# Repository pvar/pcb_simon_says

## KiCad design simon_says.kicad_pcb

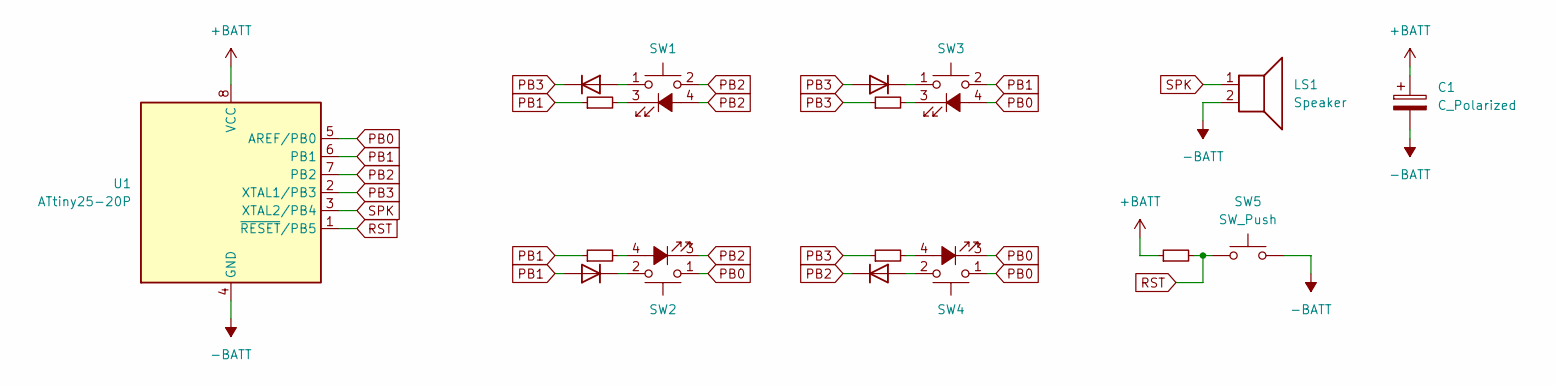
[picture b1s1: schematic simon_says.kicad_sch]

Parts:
C1: C_Polarized
D1, D2, D3, D4: 1N4004; D_DO-34_SOD68_P7.62mm_Horizontal
LS1: Speaker; PinHeader_1x02_P2.54mm_Vertical
R1, R2, R3, R4, R5: 50R; R_Axial_DIN0207_L6.3mm_D2.5mm_P7.62mm_Horizontal
SW1, SW2, SW3, SW4: SW_Push_LED; FX_tactile_12mm_with_LED
SW5: SW_Push; SW_MEC_5GSH9
U1: ATtiny25-20P; DIP-8_W7.62mm

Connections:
+BATT: C1.1, R5.1, U1.8 (VCC)
-BATT: C1.2, LS1.2, SW5.2, U1.4 (GND)
unnamed: D1.2 (A), SW1.1
unnamed: D2.1 (K), SW3.1
unnamed: D3.1 (K), SW2.2
unnamed: D4.2 (A), SW4.2
unnamed: R2.2, SW1.3 (K)
unnamed: R3.2, SW2.4 (A)
unnamed: R1.2, SW3.3 (K)
unnamed: R4.2, SW4.4 (A)
PB0: SW2.1, SW3.4 (A), SW4.1, SW4.3 (K), U1.5 (AREF/PB0)
PB1: D3.2 (A), R2.1, R3.1, SW3.2, U1.6 (PB1)
PB2: D4.1 (K), SW1.2, SW1.4 (A), SW2.3 (K), U1.7 (PB2)
PB3: D1.1 (K), D2.2 (A), R1.1, R4.1, U1.2 (XTAL1/PB3)
RST: R5.2, SW5.1, U1.1 (~RESET/PB5)
SPK: LS1.1, U1.3 (XTAL2/PB4)

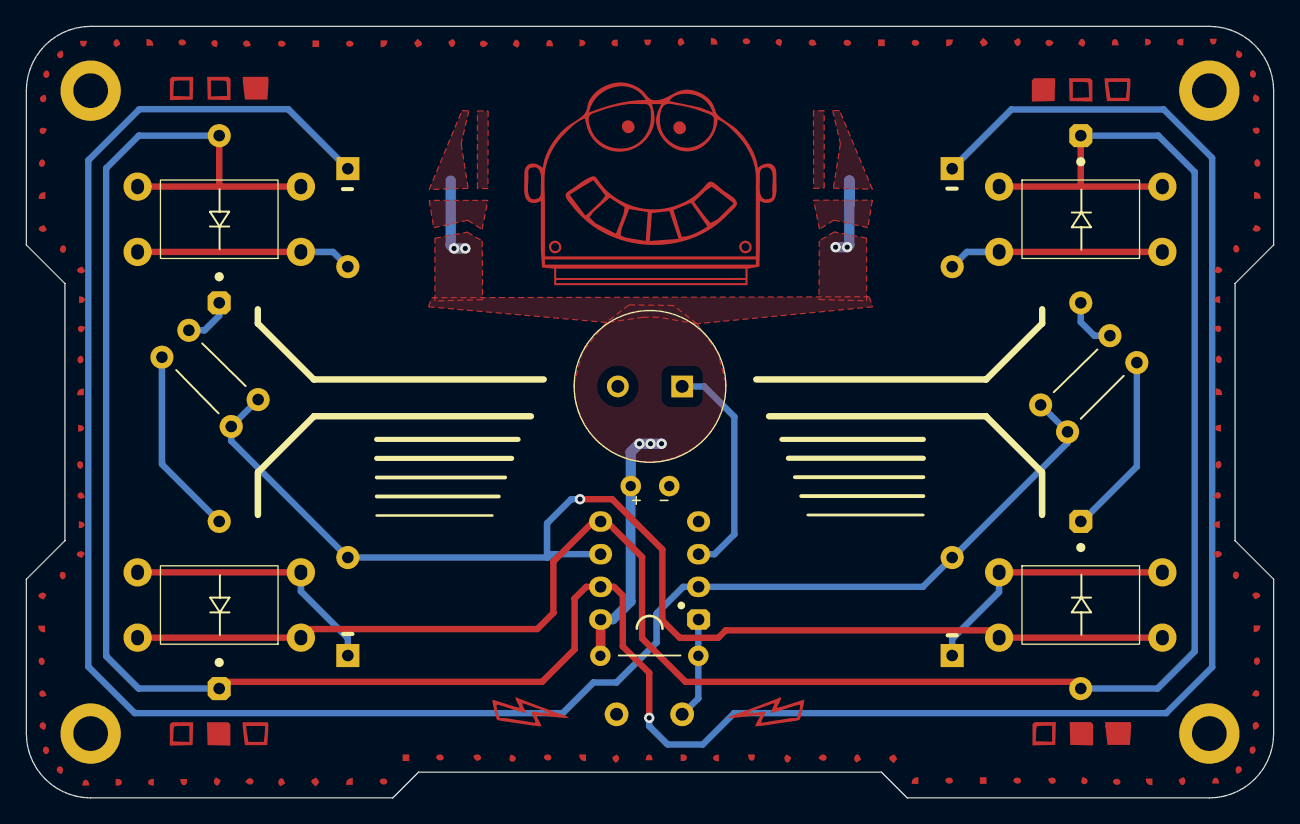
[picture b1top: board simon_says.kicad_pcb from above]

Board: 2 copper layers, 97.0 x 60.0 mm, 17 parts (0 on the bottom side), 16 nets.

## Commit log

2023-10-12 Fixed button footprint origin
2023-10-12 First take on component placement
2023-10-13 Finilized routing
2023-10-13 Added cutouts and decorations
2023-10-13 Added mounting holes
2023-10-13 Added speaker
2023-10-15 Added board pictures
2023-10-15 Finilized front face
2023-10-15 Applied aesthetic modifications
2023-10-15 Optimized routing and removed component outlines
2023-10-15 Updated board pictures
2023-10-15 Added pads for power
2023-10-23 Added CR battery pads and removed redundant LEDs
2023-10-23 Updated front face decorations
2023-10-25 The great remake! - added decoupling capacitor - replaced speaker with piezo - added 2450 cell holder - added extra button - rerouted all traces
2023-10-26 Added patches on vias of power trace
2023-10-26 Improved schematic and pcb: - added real HW reset - avoid using reset pin for IO - reroute all traces
2023-10-27 Removed unnecessary elements from silkscreen
2023-10-27 Added order number placeholder
2023-11-24 Updated front decorations
2023-12-16 Fixed traces' clearance
2024-01-04 Fixed hole size for switch contacts
2024-01-04 Small fixes on pads and vias
2024-01-05 Further enlarge hole size on pads
2024-05-01 Updated graphic elements
